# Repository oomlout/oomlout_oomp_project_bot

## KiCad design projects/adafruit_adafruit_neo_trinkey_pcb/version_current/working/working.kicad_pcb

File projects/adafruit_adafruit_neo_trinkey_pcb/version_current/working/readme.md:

# OOMP Project  
## Adafruit-Neo-Trinkey-PCB  by adafruit  
  
oomp key: oomp_projects_flat_adafruit_adafruit_neo_trinkey_pcb  
(snippet of original readme)  
  
-- Adafruit Neo Trinkey PCB  
  
<a href="http://www.adafruit.com/products/4870"><br/>  
Click here to purchase one from the Adafruit shop</a>  
  
PCB files for the Adafruit Neo Trinkey.   
  
Format is EagleCAD schematic and board layout  
* https://www.adafruit.com/product/4870  
  
--- Description  
  
It's half USB Key, half Adafruit Trinket...it's Neo Trinkey, the circuit board with a Trinket M0 heart and  four RGB NeoPixels for customizable glow. We were inspired by some USB key flashlight boards that would turn any battery pack into an LED torch. So we thought, hey what if we made something like that but with fully programmable color NeoPixels? And this is what we came up with!  
  
The PCB is designed to slip into any USB A port on a computer or laptop. There's an ATSAMD21 microcontroller on board with just enough circuitry to keep it happy. One pin of the microcontroller connects to the four NeoPixel LEDs. Two other pins are used as capacitive touch inputs on the end - if you look carefully you can see the slotted end has left and right touch pads. A reset button lets you enter bootloader mode if necessary. That's it!  
  
The SAMD21 can run CircuitPython or Arduino very nicely - with existing NeoPixel and our FreeTouch libraries for the capacitive touch input. Over the USB connection you can have serial, MIDI or HID connectivity. The Neo Trinkey is perfect for simple projects that can use a few user inputs and colorful outputs. Maybe you'll set it  
  full source readme at [readme_src.md](readme_src.md)  
  
source repo at: [https://github.com/adafruit/Adafruit-Neo-Trinkey-PCB](https://github.com/adafruit/Adafruit-Neo-Trinkey-PCB)  
## Board  

## Schematic  

[schematic pdf](working_schematic.pdf)  
## Images

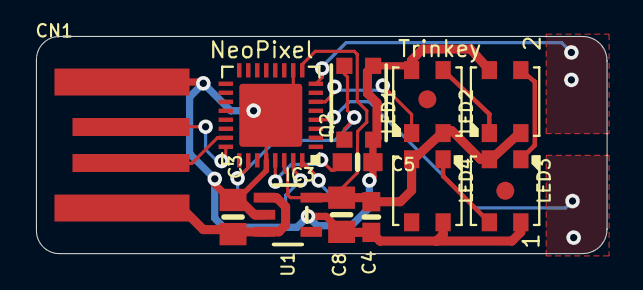
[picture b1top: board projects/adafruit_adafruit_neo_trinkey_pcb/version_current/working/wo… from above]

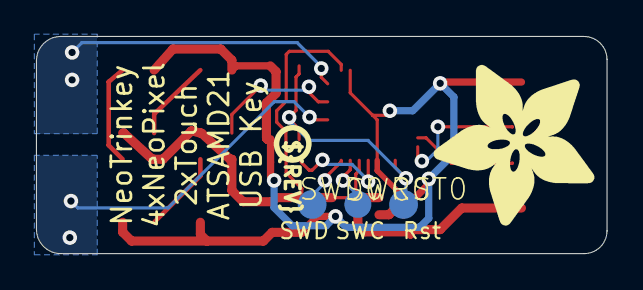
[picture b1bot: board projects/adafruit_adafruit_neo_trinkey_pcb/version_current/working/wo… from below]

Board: 2 copper layers, 31.7 x 12.1 mm, 19 parts (5 on the bottom side), 13 nets.

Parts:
C3, C8: 10uF; 0805-NO
C4, C5: 1uF; 0603-NO
CN1: USBA_PCB
FID1, FID2: FIDUCIAL_1MM
IC3: ATSAMD21E; QFN32_5MM
LED1, LED2, LED3, LED4: WS2812B3535; LED3535
Q2: reset; BTN_KMR2_4.6X2.8
RST0: TPTP16R; TP16R
SWC0: TPTP15R; TP15R
SWD0: TPTP16R; TP16R
U1: AP2112K-3.3; SOT23-5
U$8: PCBFEAT-REV-040
U$10: ADAFRUIT_9MM

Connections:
3.3V: C4.1, C8.1, IC3.9, IC3.30, LED1.2, LED2.2, LED3.2, LED4.2, U1.5
D+: CN1.USB_PLUS, IC3.24
D-: CN1.USB_NEG, IC3.23
GND: C3.2, C4.2, C5.2, C8.2, CN1.GND, IC3.10, IC3.28, IC3.33, LED1.4, LED2.4, LED3.4, LED4.4, Q2.B, Q2.B', U1.2
unnamed: LED1.3, LED2.1
unnamed: LED2.3, LED3.1
unnamed: LED3.3, LED4.1
NEOPIX: IC3.6, LED1.1
SWCLK: IC3.31, SWC0.TP
SWDIO: IC3.32, SWD0.TP
VBUS: C3.1, CN1.VCC, U1.1, U1.3
VDDCORE1: C5.1, IC3.29
~RESET: IC3.26, Q2.A, Q2.A', RST0.TP

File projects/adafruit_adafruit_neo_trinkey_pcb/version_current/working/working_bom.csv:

Row,Description,Part,References,Value,Footprint,Quantity Per PCB,Status,Datasheet
1,,CAP_CERAMIC0603_NO,C4 C5,1uF,0603-NO,2, ,
2,,CAP_CERAMIC0805-NOOUTLINE,C3 C8,10uF,0805-NO,2, ,
3,,USB_TYPEAPCB,CN1,USB_TYPEAPCB,USBA_PCB,1, ,
4,,ATSAMD21E,IC3,ATSAMD21E,QFN32_5MM,1, ,
5,,WS2812B3535,LED1 LED2 LED3 LED4,WS2812B3535,LED3535,4, ,
6,,SWITCH_TACT_SMT4.6X2.8,Q2,reset,BTN_KMR2_4.6X2.8,1, ,
7,,TPTP16R,RST0 SWD0,TPTP16R,TP16R,2, ,
8,,TPTP15R,SWC0,TPTP15R,TP15R,1, ,
9,,VREG_SOT23-5,U1,AP2112K-3.3,SOT23-5,1, ,





Project info:
Schematic:,working
Variant:,default
Revision:,
Date:,2023-08-03_17-21-22
KiCad Version:,7.0.6-7.0.6~ubuntu22.04.1
Statistics:
Component Groups:,9
Component Count:,15 (0 SMD/ 0 THT)
Fitted Components:,15 (0 SMD/ 0 THT)
Number of PCBs:,1
Total Components:,15

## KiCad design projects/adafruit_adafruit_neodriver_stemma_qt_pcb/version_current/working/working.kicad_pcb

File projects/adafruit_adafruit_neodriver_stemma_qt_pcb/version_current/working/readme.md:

# Adafruit-NeoDriver-STEMMA-QT-PCB by adafruit  
This is a harvested standardized copy of a project from github.  
The original project can be found at:  
https://github.com/adafruit/Adafruit-NeoDriver-STEMMA-QT-PCB  
Please consult that link for additional, details, files, and license information.  
Note: It was auto harvested and if the original repo had more than one board file or anything out of the ordinary the files here are likely not representative.

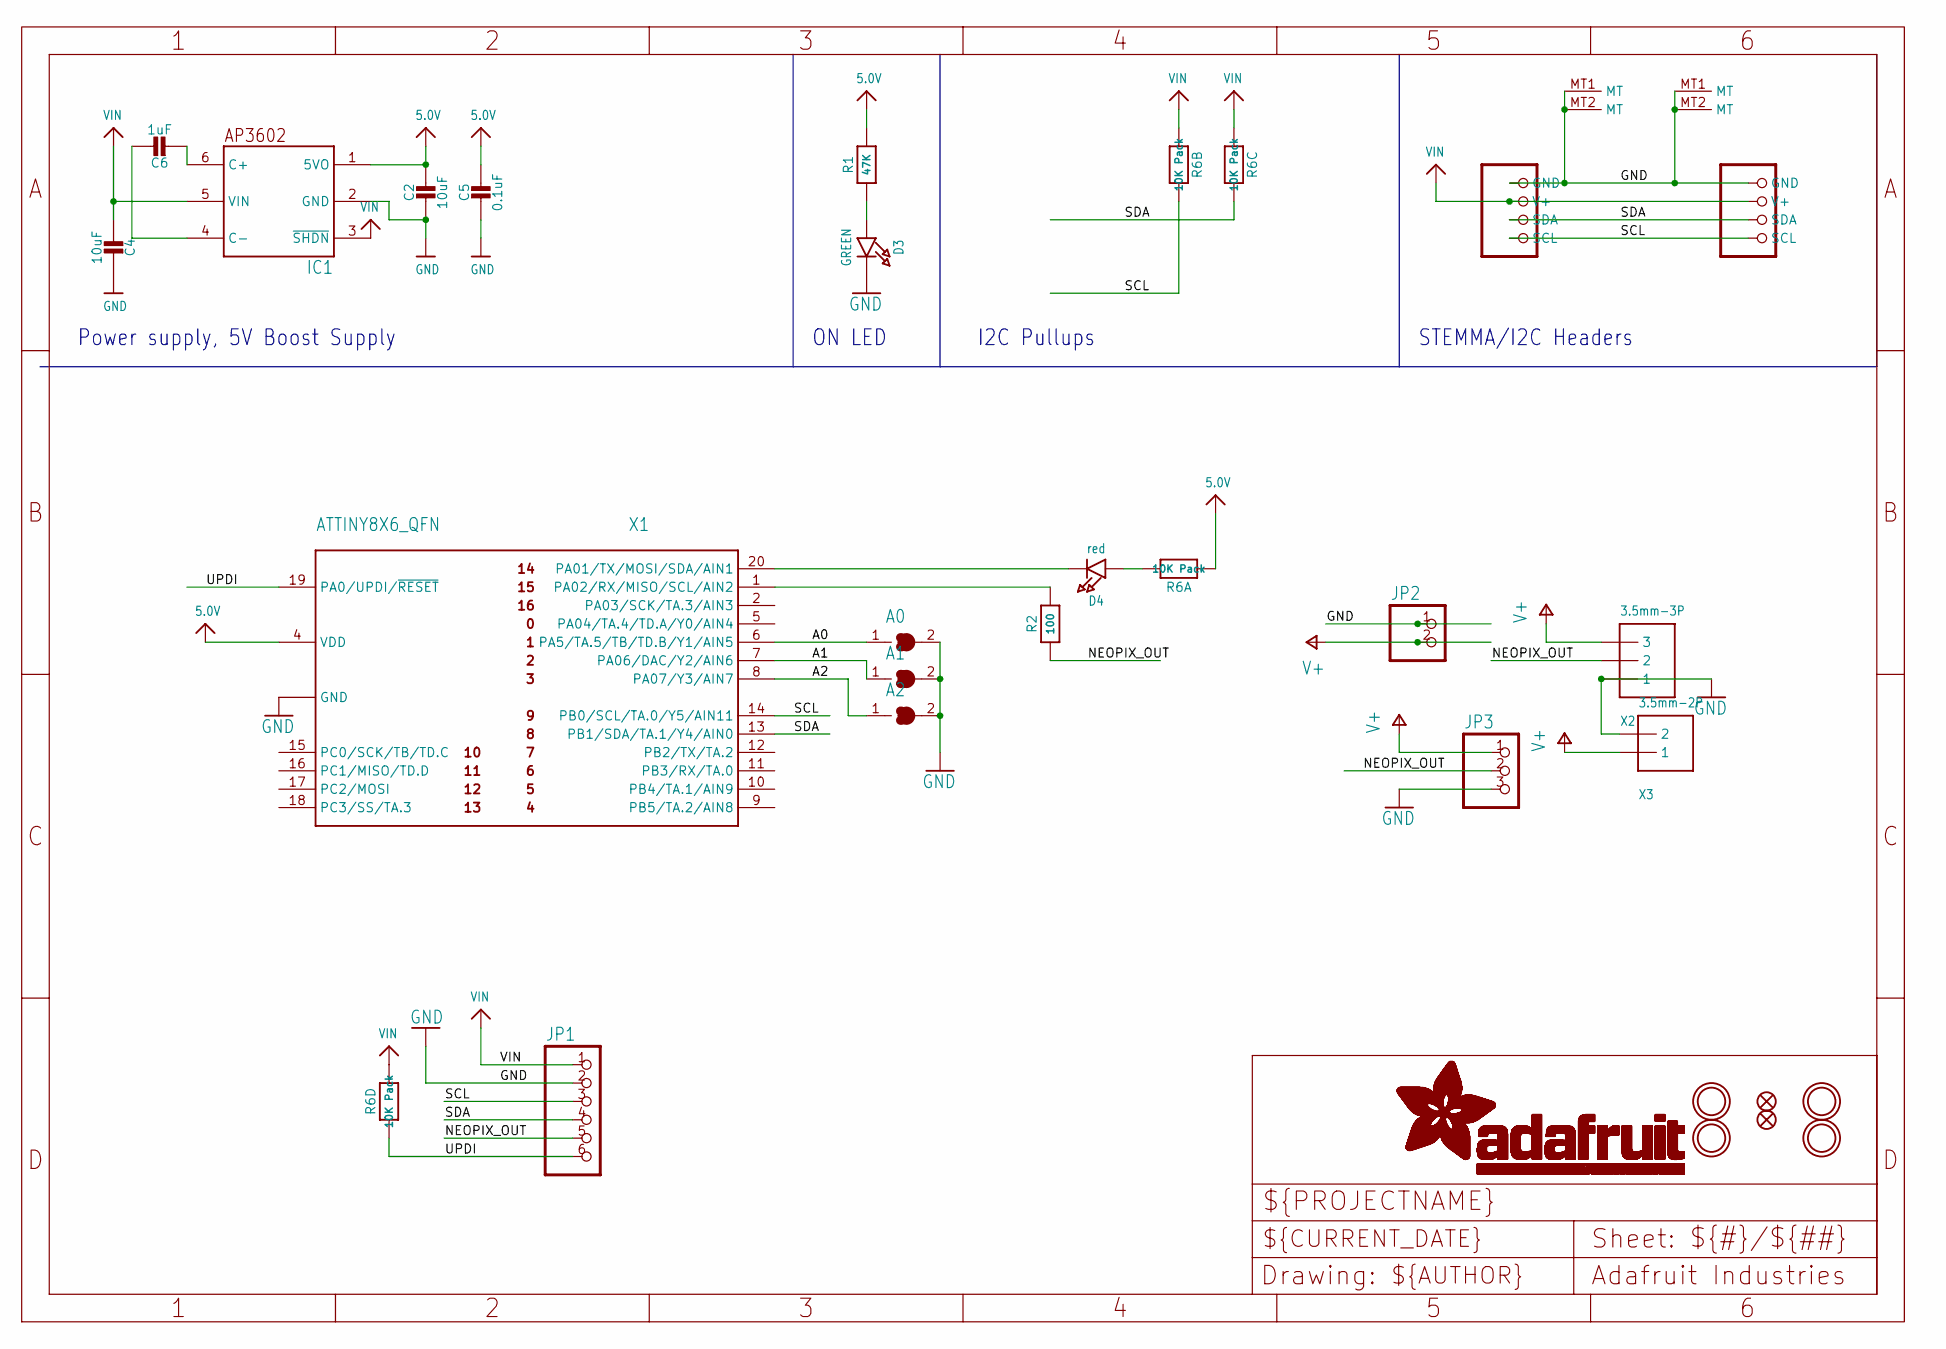
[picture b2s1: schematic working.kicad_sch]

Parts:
A0, A1, A2: SOLDERJUMPER_CLOSED; SOLDERJUMPER_CLOSEDWIRE
C2, C4: 10uF; 0805-NO
C5: 0.1uF; 0603-NO
C6: 1uF; 0603-NO
CONN3, CONN4: STEMMA_I2C_QT; JST_SH4
D3: GREEN; CHIPLED_0603_NOOUTLINE
D4: red; CHIPLED_0603_NOOUTLINE
FID1, FID2: FIDUCIAL_1MM
IC1: AP3602; SOT23-6
JP1: HEADER-1X670MIL; 1X06_ROUND_70
JP2: HEADER-1X2ROUND; 1X02_ROUND
JP3: HEADER-1X3ROUND; 1X03_ROUND
R1: 47K; 0603-NO
R2: 100; 0603-NO
R6: 10K Pack; RESPACK_4X0603
U$1, U$6, U$9, U$18: MOUNTINGHOLE2.5; MOUNTINGHOLE_2.5_PLATED
X1: ATTINY8X6_QFN; QFN20_3MM
X2: 3.5mm-3P; TERMBLOCK_1X3-3.5MM
X3: 3.5mm-2P; TERMBLOCK_1X2-3.5MM

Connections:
5.0V: C2.1, C5.1, IC1.1 (5VO), R1.2, R6.1, X1.4 (VDD)
A0: A0.1, X1.6 (PA5/TA.5/TB/TD.B/Y1/AIN5)
A1: A1.1, X1.7 (PA06/DAC/Y2/AIN6)
A2: A2.1, X1.8 (PA07/Y3/AIN7)
ACT: D4.C, X1.20 (PA01/TX/MOSI/SDA/AIN1)
GND: A0.2, A1.2, A2.2, C2.2, C4.2, C5.2, CONN3.1 (GND), CONN3.MT1 (MT), CONN3.MT2 (MT), CONN4.1 (GND), CONN4.MT1 (MT), CONN4.MT2 (MT), D3.C, IC1.2 (GND), JP1.2, JP2.1, JP3.3, X1.3 (GND), X1.PAD (GND), X2.1, X3.2
unnamed: D3.A, R1.1
unnamed: C6.2, IC1.6 (C+)
unnamed: C6.1, IC1.4 (C-)
unnamed: D4.A, R6.8 (2)
unnamed: R2.2, X1.1 (PA02/RX/MISO/SCL/AIN2)
NEOPIX_OUT: JP1.5, JP3.2, R2.1, X2.2
SCL: CONN3.4 (SCL), CONN4.4 (SCL), JP1.3, R6.7 (2), X1.14 (PB0/SCL/TA.0/Y5/AIN11)
SDA: CONN3.3 (SDA), CONN4.3 (SDA), JP1.4, R6.6 (2), X1.13 (PB1/SDA/TA.1/Y4/AIN0)
UPDI: JP1.6, R6.4 (1), X1.19 (PA0/UPDI/~RESET)
V+: JP2.2, JP3.1, X2.3, X3.1
VIN: C4.1, CONN3.2 (V+), CONN4.2 (V+), IC1.3 (~SHDN), IC1.5 (VIN), JP1.1, R6.2 (1), R6.3 (1), R6.5 (2)

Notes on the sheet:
ON LED
Power supply, 5V Boost Supply
I2C Pullups
STEMMA/I2C Headers

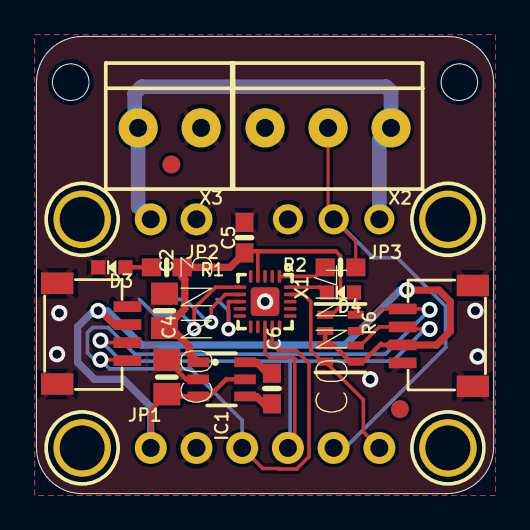
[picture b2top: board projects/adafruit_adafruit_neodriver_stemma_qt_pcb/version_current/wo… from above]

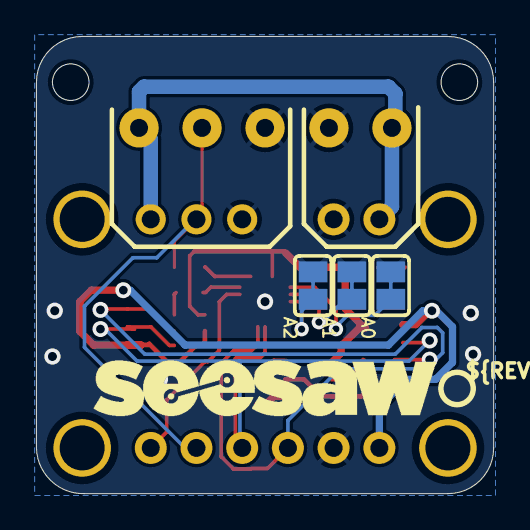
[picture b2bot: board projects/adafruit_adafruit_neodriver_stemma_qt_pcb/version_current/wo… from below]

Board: 2 copper layers, 25.4 x 25.4 mm, 61 parts (17 on the bottom side), 17 nets.

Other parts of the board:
@HOLE0, @HOLE1: (no value)
PLABEL0: PLABEL0
PLABEL1: PLABEL1
PLABEL2: PLABEL2
PLABEL3: PLABEL3
PLABEL4: PLABEL4
PLABEL5: PLABEL5
PLABEL6: PLABEL6
PLABEL7: PLABEL7
PLABEL8: PLABEL8
PLABEL9: PLABEL9
PLABEL10: PLABEL10
PLABEL11: PLABEL11
PLABEL12: PLABEL12
PLABEL13: PLABEL13
PLABEL14: PLABEL14
PLABEL15: PLABEL15
PLABEL16: PLABEL16
PLABEL17: PLABEL17
PLABEL18: PLABEL18
PLABEL19: PLABEL19
PLABEL20: PLABEL20
PLABEL21: PLABEL21
PLABEL22: PLABEL22
PLABEL23: PLABEL23
PLABEL24: PLABEL24
PLABEL25: PLABEL25
PLABEL26: PLABEL26
PLABEL27: PLABEL27
PLABEL28: PLABEL28
PLABEL29: PLABEL29
U$7: SEESAW_LOGO
U$12: PCBFEAT-REV-040

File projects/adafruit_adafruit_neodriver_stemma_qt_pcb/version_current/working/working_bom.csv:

Row,Description,Part,References,Value,Footprint,Quantity Per PCB,Status,Datasheet
1,,CAP_CERAMIC0603_NO,C5,0.1uF,0603-NO,1, ,
2,,CAP_CERAMIC0603_NO,C6,1uF,0603-NO,1, ,
3,,CAP_CERAMIC0805-NOOUTLINE,C2 C4,10uF,0805-NO,2, ,
4,,STEMMA_I2C_QT,CONN3 CONN4,STEMMA_I2C_QT,JST_SH4,2, ,
5,,LED0603_NOOUTLINE,D3,GREEN,CHIPLED_0603_NOOUTLINE,1, ,
6,,LED0603_NOOUTLINE,D4,red,CHIPLED_0603_NOOUTLINE,1, ,
7,,AP3602,IC1,AP3602,SOT23-6,1, ,
8,,HEADER-1X2ROUND,JP2,HEADER-1X2ROUND,1X02_ROUND,1, ,
9,,HEADER-1X3ROUND,JP3,HEADER-1X3ROUND,1X03_ROUND,1, ,
10,,HEADER-1X670MIL,JP1,HEADER-1X670MIL,1X06_ROUND_70,1, ,
11,,RESISTOR_0603_NOOUT,R2,100,0603-NO,1, ,
12,,RESISTOR_4PACK,R6,10K Pack,RESPACK_4X0603,1, ,
13,,RESISTOR_0603_NOOUT,R1,47K,0603-NO,1, ,
14,,TERMBLOCK_1X2_3.5MM,X3,3.5mm-2P,TERMBLOCK_1X2-3.5MM,1, ,
15,,TERMBLOCK_1X3,X2,3.5mm-3P,TERMBLOCK_1X3-3.5MM,1, ,
16,,ATTINY8X6_QFN,X1,ATTINY8X6_QFN,QFN20_3MM,1, ,





Project info:
Schematic:,working
Variant:,default
Revision:,
Date:,2023-08-03_17-21-22
KiCad Version:,7.0.6-7.0.6~ubuntu22.04.1
Statistics:
Component Groups:,16
Component Count:,18 (0 SMD/ 0 THT)
Fitted Components:,18 (0 SMD/ 0 THT)
Number of PCBs:,1
Total Components:,18

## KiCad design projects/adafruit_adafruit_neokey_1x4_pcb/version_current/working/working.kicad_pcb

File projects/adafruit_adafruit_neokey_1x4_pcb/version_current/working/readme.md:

# Adafruit-NeoKey-1x4-PCB by adafruit  
This is a harvested standardized copy of a project from github.  
The original project can be found at:  
https://github.com/adafruit/Adafruit-NeoKey-1x4-PCB  
Please consult that link for additional, details, files, and license information.  
Note: It was auto harvested and if the original repo had more than one board file or anything out of the ordinary the files here are likely not representative.

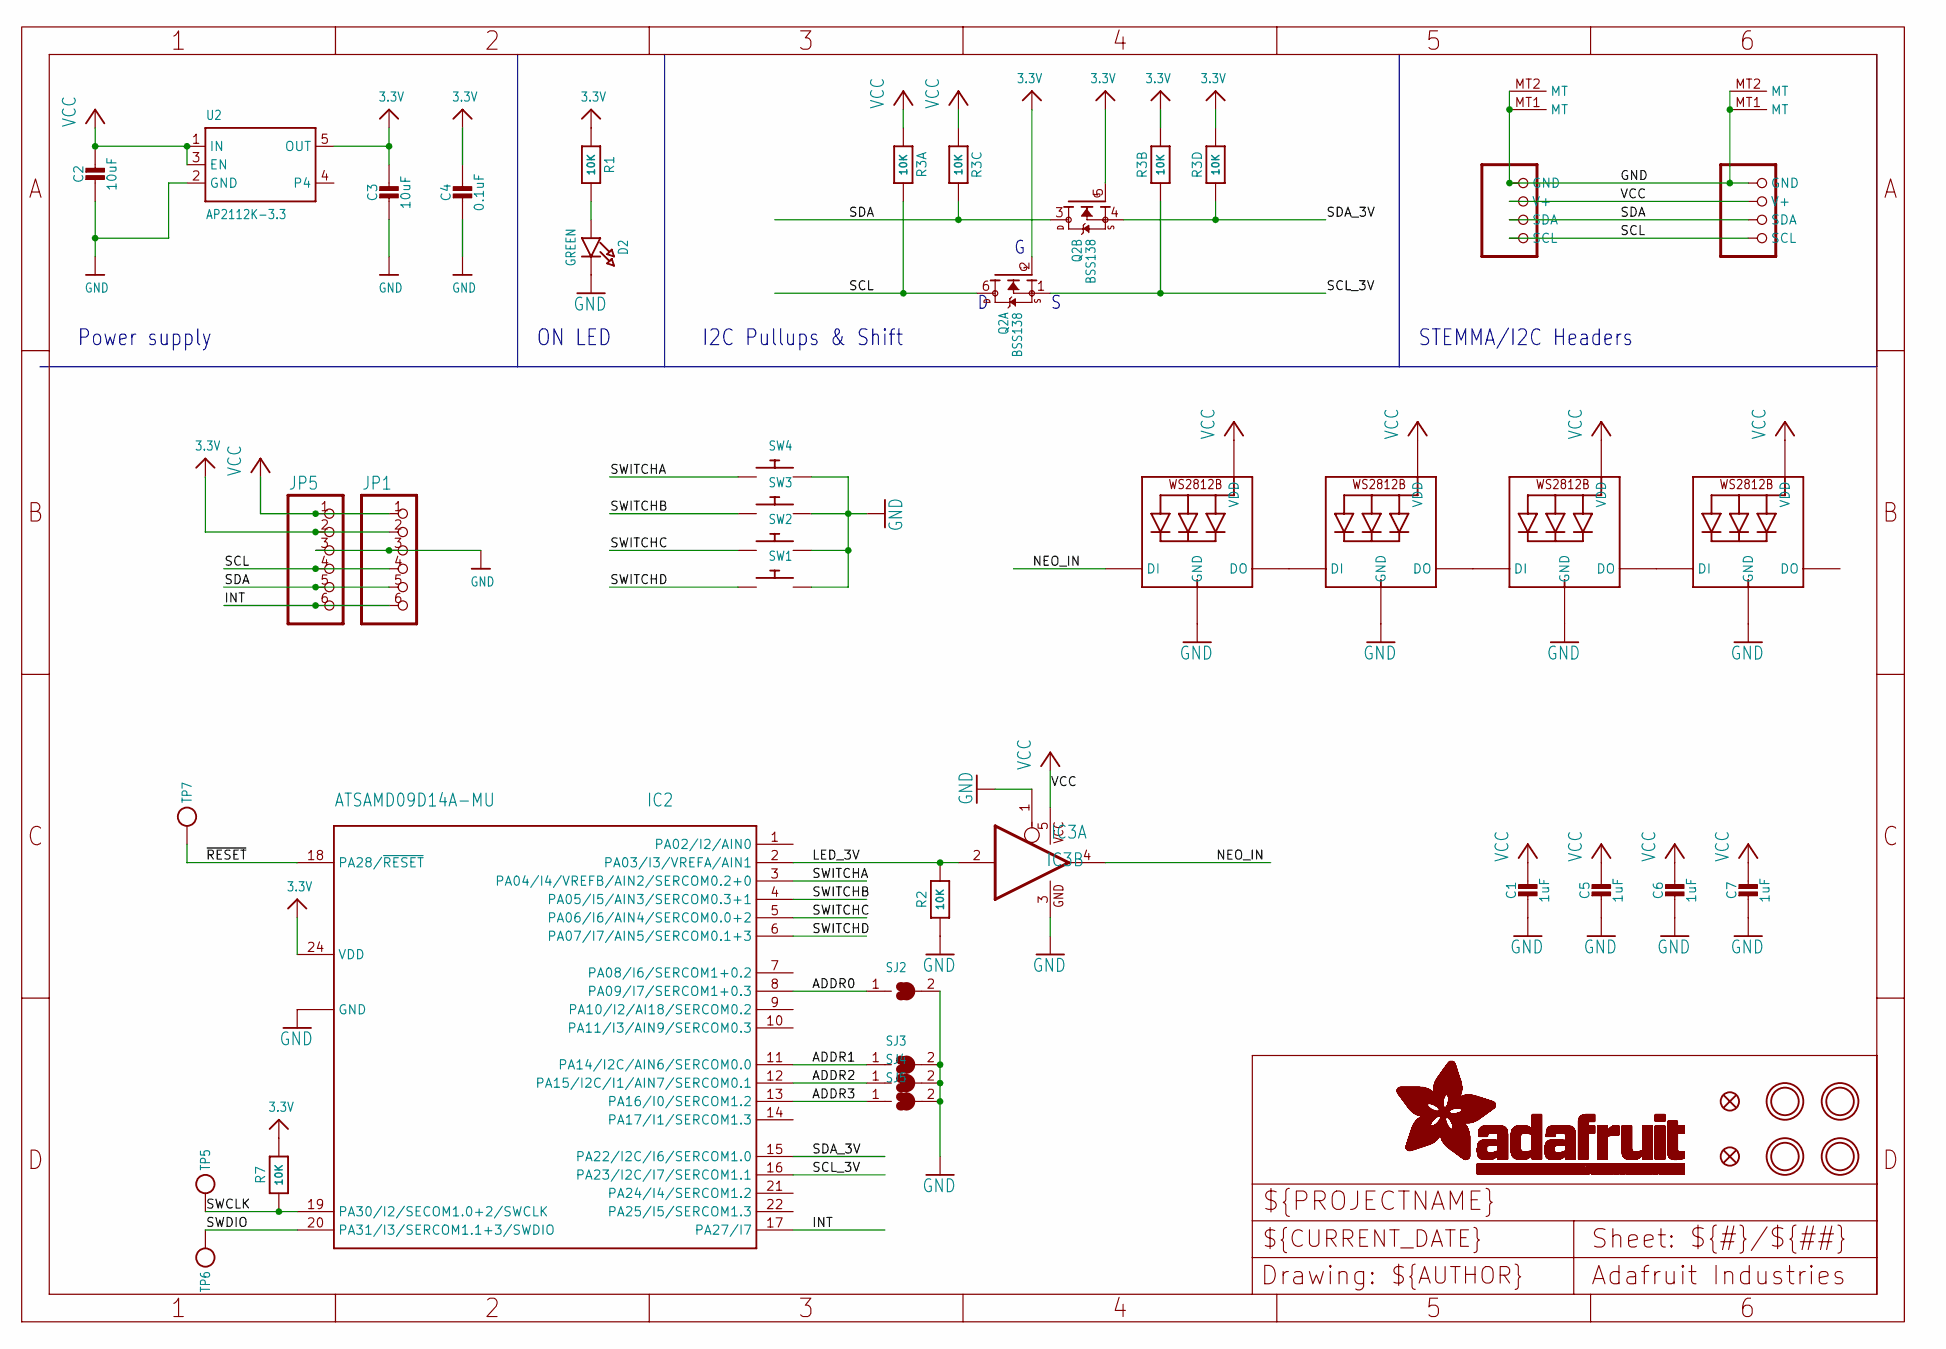
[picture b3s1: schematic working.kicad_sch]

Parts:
C1, C5, C6, C7: 1uF; 0603-NO
C2, C3: 10uF; 0805-NO
C4: 0.1uF; 0603-NO
CONN3, CONN4: STEMMA_I2C_QT; JST_SH4
D2: GREEN; CHIPLED_0603_NOOUTLINE
FID1, FID2: FIDUCIAL_1MM
IC2: ATSAMD09D14A-MU; QFN24_4MM
IC3: 741G125DBV; SOT23-5
JP1, JP5: HEADER-1X670MIL; 1X06_ROUND_70
LED1, LED2, LED3, LED4: WS2812B_SK6812E; NEO3535_REVERSE
Q2: BSS138; SOT363
R1, R2, R7: 10K; 0603-NO
R3: 10K; RESPACK_4X0603
SJ2, SJ3, SJ4, SJ5: SOLDERJUMPER; SOLDERJUMPER_ARROW_NOPASTE
SW1, SW2, SW3, SW4: SWITCH_PUSHBUTTON_KAILH_SOCKET; KAILH_SOCKET
TP5, TP6, TP7: TESTPOINTROUND1.5MM; TESTPOINT_ROUND_1.5MM
U2: AP2112K-3.3; SOT23-5
U$3, U$17, U$19, U$21: MOUNTINGHOLE2.5; MOUNTINGHOLE_2.5_PLATED

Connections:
3.3V: C3.1, C4.1, IC2.24 (VDD), JP1.2, JP5.2, Q2.2 (G), Q2.5 (G), R1.1, R3.2 (1), R3.4 (1), R7.2, U2.5 (OUT)
ADDR0: IC2.8 (PA09/I7/SERCOM1+0.3), SJ2.1
ADDR1: IC2.11 (PA14/I2C/AIN6/SERCOM0.0), SJ3.1
ADDR2: IC2.12 (PA15/I2C/I1/AIN7/SERCOM0.1), SJ4.1
ADDR3: IC2.13 (PA16/I0/SERCOM1.2), SJ5.1
GND: C1.2, C2.2, C3.2, C4.2, C5.2, C6.2, C7.2, CONN3.1 (GND), CONN3.MT1 (MT), CONN3.MT2 (MT), CONN4.1 (GND), CONN4.MT1 (MT), CONN4.MT2 (MT), D2.C, IC2.23 (GND), IC2.THERM (GND), IC3.1 (OE), IC3.3 (GND), JP1.3, JP5.3, LED1.3-GND (GND), LED2.3-GND (GND), LED3.3-GND (GND), LED4.3-GND (GND), R2.1, SJ2.2, SJ3.2, SJ4.2, SJ5.2, SW1.1, SW2.1, SW3.1, SW4.1, U2.2 (GND)
INT: IC2.17 (PA27/I7), JP1.6, JP5.6
LED_3V: IC2.2 (PA03/I3/VREFA/AIN1), IC3.2 (I), R2.2
unnamed: D2.A, R1.2
unnamed: LED1.2-DOUT (DO), LED2.4-DIN (DI)
unnamed: LED2.2-DOUT (DO), LED3.4-DIN (DI)
unnamed: LED3.2-DOUT (DO), LED4.4-DIN (DI)
NEO_IN: IC3.4 (O), LED1.4-DIN (DI)
SCL: CONN3.4 (SCL), CONN4.4 (SCL), JP1.4, JP5.4, Q2.6 (D), R3.8 (2)
SCL_3V: IC2.16 (PA23/I2C/I7/SERCOM1.1), Q2.1 (S), R3.7 (2)
SDA: CONN3.3 (SDA), CONN4.3 (SDA), JP1.5, JP5.5, Q2.3 (D), R3.6 (2)
SDA_3V: IC2.15 (PA22/I2C/I6/SERCOM1.0), Q2.4 (S), R3.5 (2)
SWCLK: IC2.19 (PA30/I2/SECOM1.0+2/SWCLK), R7.1, TP5.P$1
SWDIO: IC2.20 (PA31/I3/SERCOM1.1+3/SWDIO), TP6.P$1
SWITCHA: IC2.3 (PA04/I4/VREFB/AIN2/SERCOM0.2+0), SW4.2
SWITCHB: IC2.4 (PA05/I5/AIN3/SERCOM0.3+1), SW3.2
SWITCHC: IC2.5 (PA06/I6/AIN4/SERCOM0.0+2), SW2.2
SWITCHD: IC2.6 (PA07/I7/AIN5/SERCOM0.1+3), SW1.2
VCC: C1.1, C2.1, C5.1, C6.1, C7.1, CONN3.2 (V+), CONN4.2 (V+), IC3.5 (VCC), JP1.1, JP5.1, LED1.1-VDD (VDD), LED2.1-VDD (VDD), LED3.1-VDD (VDD), LED4.1-VDD (VDD), R3.1, R3.3 (1), U2.1 (IN), U2.3 (EN)
~RESET: IC2.18 (PA28/~RESET), TP7.P$1

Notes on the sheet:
ON LED
I2C Pullups & Shift
Power supply
STEMMA/I2C Headers

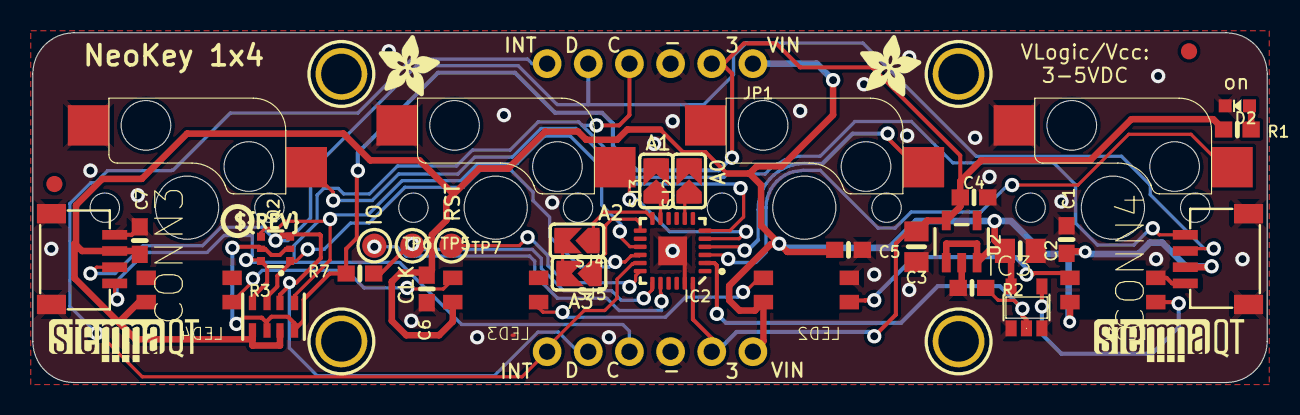
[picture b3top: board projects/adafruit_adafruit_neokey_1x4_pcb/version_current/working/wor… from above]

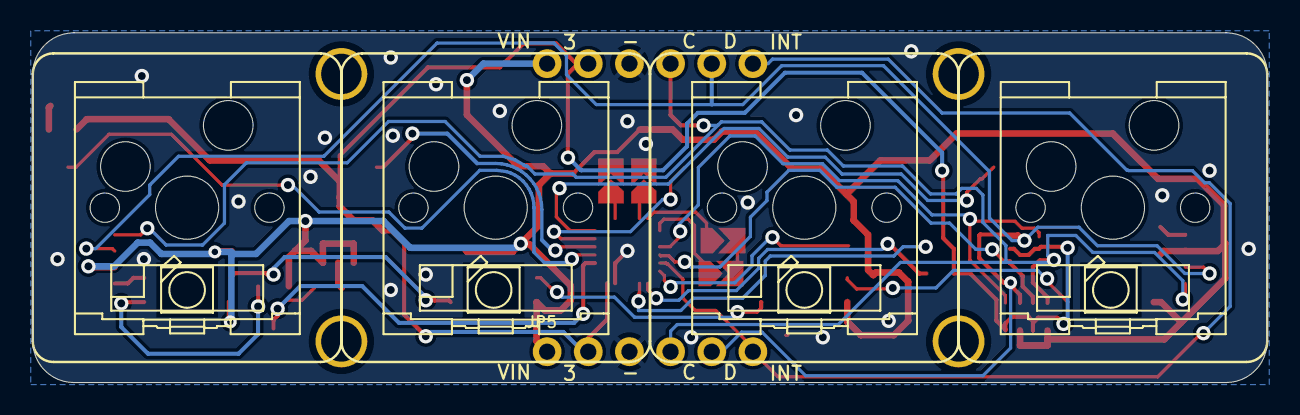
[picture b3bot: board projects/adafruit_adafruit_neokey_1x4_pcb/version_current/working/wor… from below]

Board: 2 copper layers, 76.2 x 21.6 mm, 46 parts (9 on the bottom side), 25 nets.

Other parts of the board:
U$2, U$9: ADAFRUIT_3.5MM
U$25: PCBFEAT-REV-040
U$30, U$31: STEMMAQT

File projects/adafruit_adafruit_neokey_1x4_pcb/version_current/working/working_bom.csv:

Row,Description,Part,References,Value,Footprint,Quantity Per PCB,Status,Datasheet
1,,CAP_CERAMIC0603_NO,C4,0.1uF,0603-NO,1, ,
2,,CAP_CERAMIC0603_NO,C1 C5 C6 C7,1uF,0603-NO,4, ,
3,,CAP_CERAMIC0805-NOOUTLINE,C2 C3,10uF,0805-NO,2, ,
4,,STEMMA_I2C_QT,CONN3 CONN4,STEMMA_I2C_QT,JST_SH4,2, ,
5,,LED0603_NOOUTLINE,D2,GREEN,CHIPLED_0603_NOOUTLINE,1, ,
6,,741G125DBV,IC3,741G125DBV,SOT23-5,1, ,
7,,ATSAMD09D14A-MU,IC2,ATSAMD09D14A-MU,QFN24_4MM,1, ,
8,,HEADER-1X670MIL,JP1 JP5,HEADER-1X670MIL,1X06_ROUND_70,2, ,
9,,WS2812B_SK6812E,LED1 LED2 LED3 LED4,WS2812B_SK6812E,NEO3535_REVERSE,4, ,
10,,MOSFET-N_DUAL,Q2,BSS138,SOT363,1, ,
11,,RESISTOR_0603_NOOUT,R1 R2 R7,10K,0603-NO,3, ,
12,,RESISTOR_4PACK,R3,10K,RESPACK_4X0603,1, ,
13,,SWITCH_PUSHBUTTON_KAILH_SOCKET,SW1 SW2 SW3 SW4,SWITCH_PUSHBUTTON_KAILH_SOCKET,KAILH_SOCKET,4, ,
14,,VREG_SOT23-5,U2,AP2112K-3.3,SOT23-5,1, ,





Project info:
Schematic:,working
Variant:,default
Revision:,
Date:,2023-08-03_17-21-22
KiCad Version:,7.0.6-7.0.6~ubuntu22.04.1
Statistics:
Component Groups:,14
Component Count:,28 (0 SMD/ 0 THT)
Fitted Components:,28 (0 SMD/ 0 THT)
Number of PCBs:,1
Total Components:,28

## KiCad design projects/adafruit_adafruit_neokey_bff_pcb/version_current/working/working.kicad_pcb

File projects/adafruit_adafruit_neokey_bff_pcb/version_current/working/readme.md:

# OOMP Project  
## Adafruit-NeoKey-BFF-PCB  by adafruit  
  
oomp key: oomp_projects_flat_adafruit_adafruit_neokey_bff_pcb  
(snippet of original readme)  
  
-- Adafruit NeoKey BFF for Mechanical Key Add-On for QT Py and Xiao - For MX Compatible Switches PCB  
  
<a href="http://www.adafruit.com/products/5695"><br/>  
Click here to purchase one from the Adafruit shop</a>  
  
PCB files for the Adafruit NeoKey BFF for Mechanical Key Add-On for QT Py and Xiao - For MX Compatible Switches.   
  
Format is EagleCAD schematic and board layout  
* https://www.adafruit.com/product/5695  
  
--- Description  
  
Our QT Py boards are a great way to make very small microcontroller projects that pack a ton of power - and now we have a way for you to quickly add a nice mechanical key that also can glow any color of the rainbow.   
  
We call this the Adafruit NeoKey BFF - a "Best Friend Forever". When you were a kid you may have learned about the "buddy" system, well this product is kinda like that! A board that will watch your QT Py's back and give it more capabilities.  
  
This PCB is designed to fit onto the back of any QT Py or Xiao board; it can be soldered into place or use pin and socket headers to make it removable. Onboard is a Kailh socket, which means you can plug in any MX-compatible switch instead of soldering it in. You may need a little glue to keep the switch in place: hot glue or a dot of epoxy worked fine for us. Also comes with a single reverse-mount NeoPixel pointing up through the spot where many switches would have an LED to shine through.  
  
We include some header that you can solder to your QT Py. Y  
  full source readme at [readme_src.md](readme_src.md)  
  
source repo at: [https://github.com/adafruit/Adafruit-NeoKey-BFF-PCB](https://github.com/adafruit/Adafruit-NeoKey-BFF-PCB)  
## Board  

## Schematic  

[schematic pdf](working_schematic.pdf)  
## Images

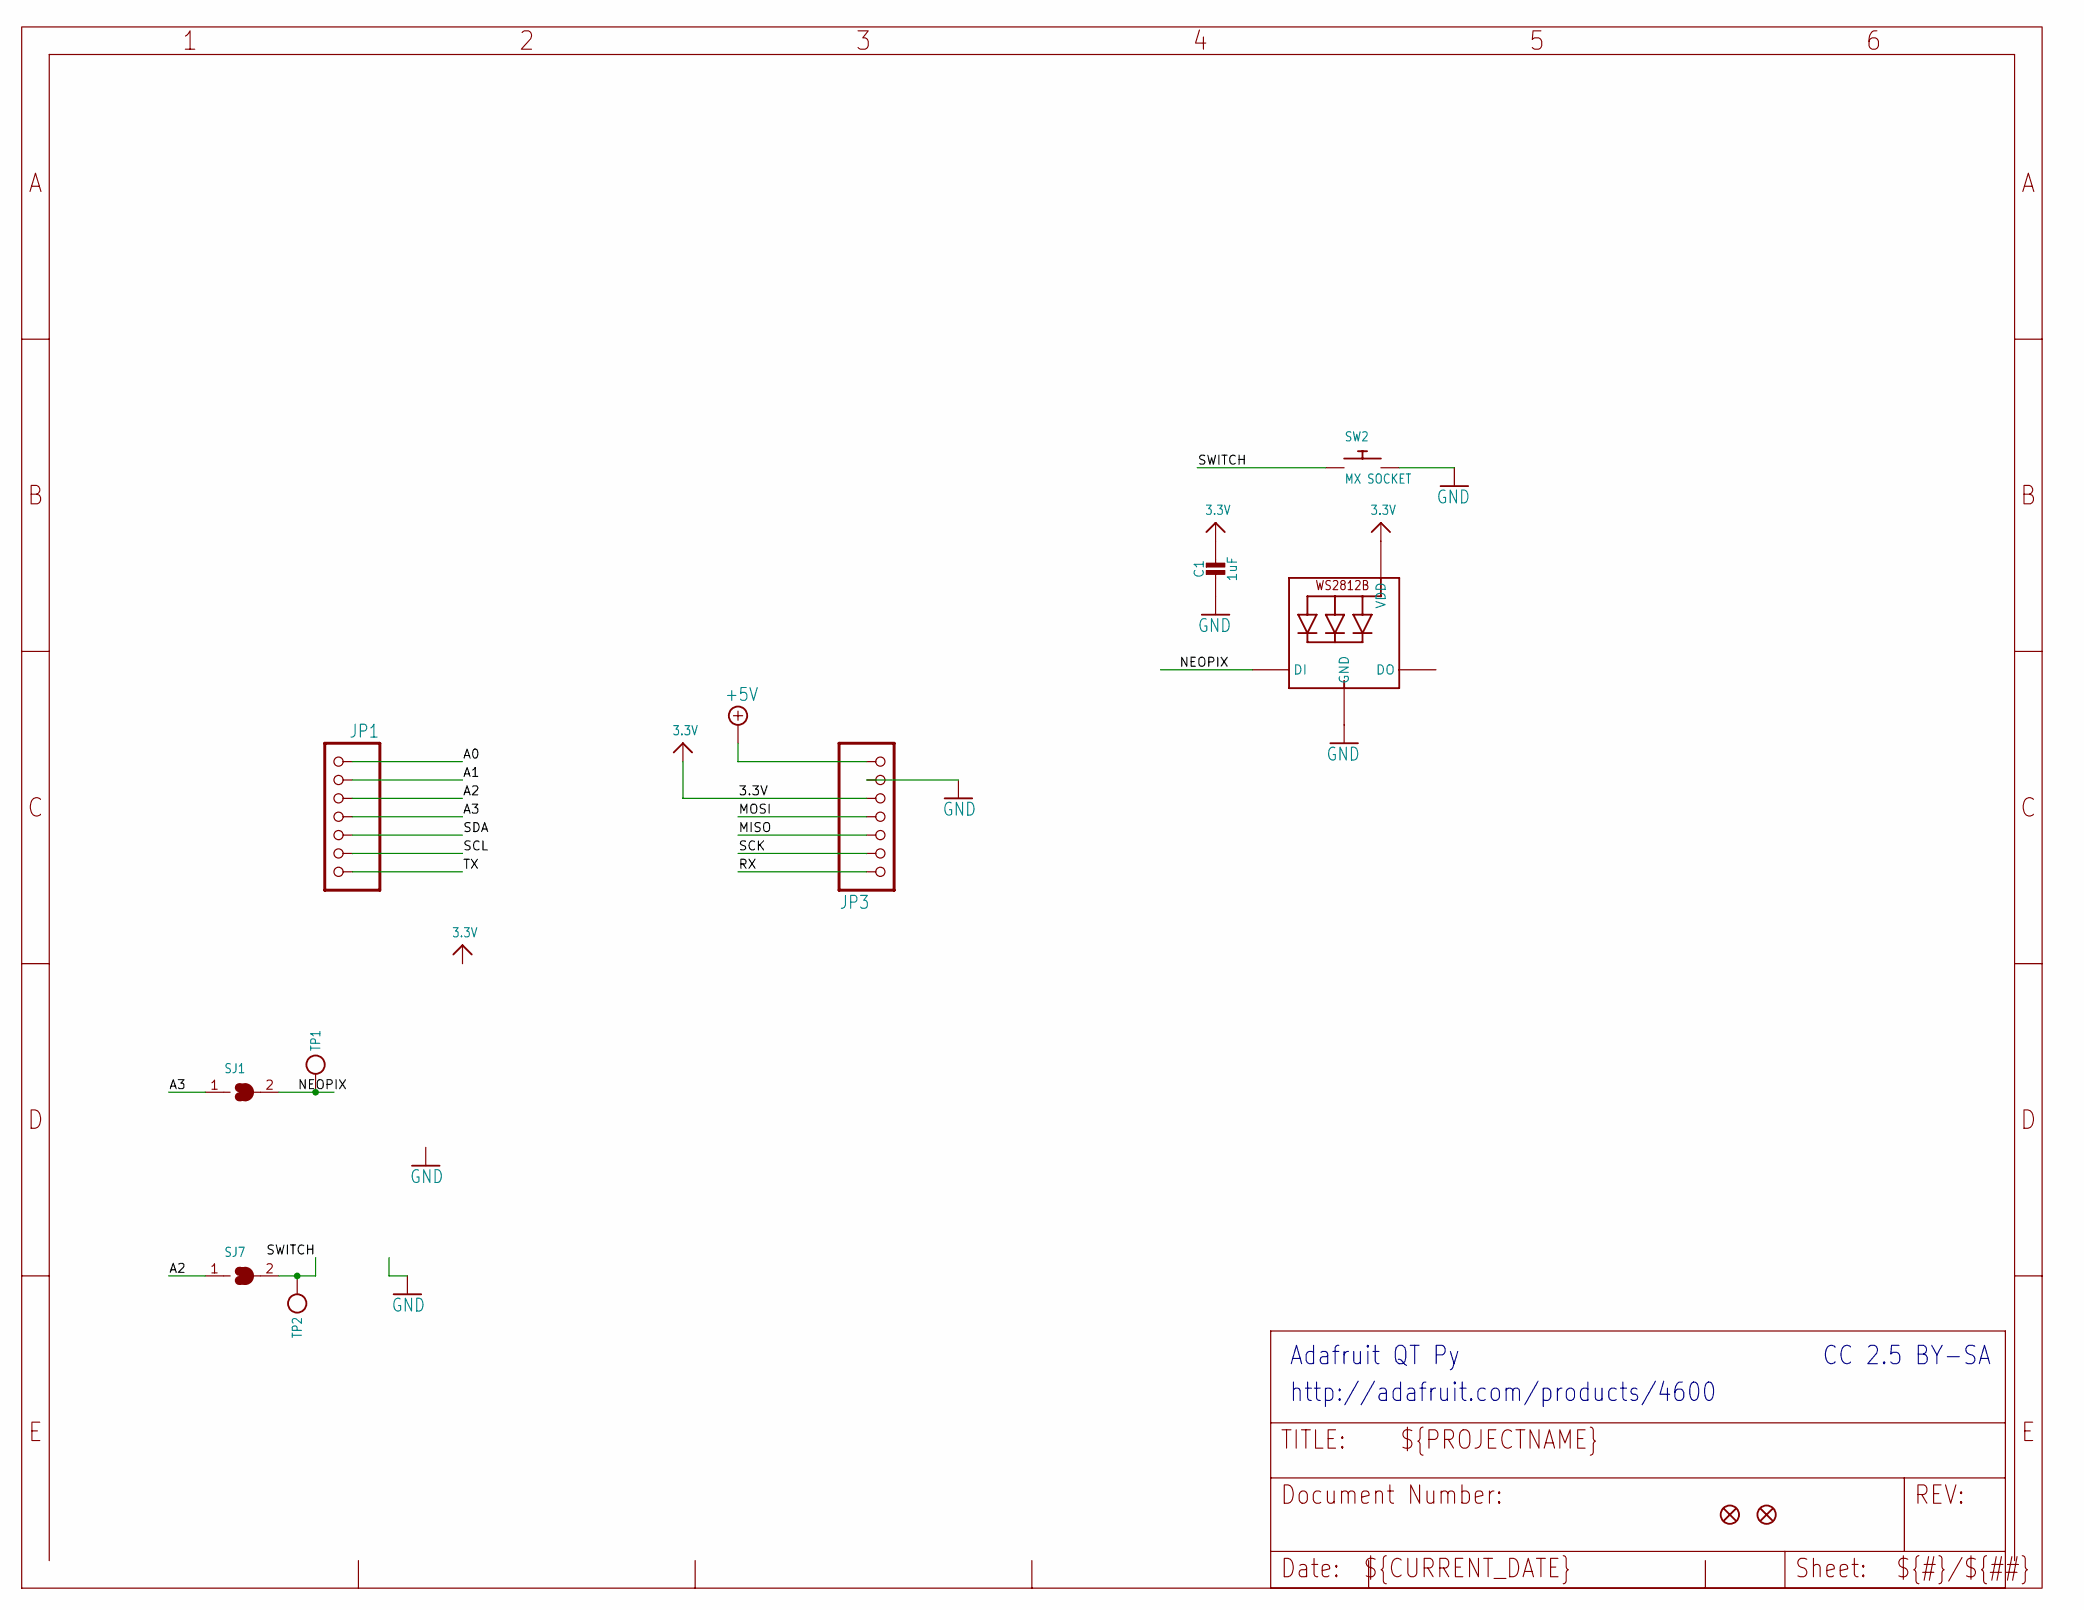
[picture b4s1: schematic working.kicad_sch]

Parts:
C1: 1uF; 0603-NO
JP1, JP3: HEADER-1X7_CASTEL; 1X07_CASTEL
LED2: WS2812B_SK6812E; NEO3535_REVERSE
SJ1, SJ7: SOLDERJUMPERCLOSED; SOLDERJUMPER_CLOSEDWIRE
SW2: MX SOCKET; KAILH_SOCKET
TP1, TP2: TESTPOINT1.5X2.0MM_NOCREAM; PAD-1.5X2.0
U$6, U$8: FIDUCIAL_1MM

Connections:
3.3V: C1.1, JP3.5, JP3.5C (5), LED2.1-VDD (VDD)
+5V: JP3.7, JP3.7C (7)
A0: JP1.1, JP1.1C (1)
A1: JP1.2, JP1.2C (2)
A2: JP1.3, JP1.3C (3), SJ7.1
A3: JP1.4, JP1.4C (4), SJ1.1
GND: C1.2, JP3.6, JP3.6C (6), LED2.3-GND (GND), SW2.2
MISO: JP3.3, JP3.3C (3)
MOSI: JP3.4, JP3.4C (4)
NEOPIX: LED2.4-DIN (DI), SJ1.2, TP1.P$1
RX: JP3.1, JP3.1C (1)
SCK: JP3.2, JP3.2C (2)
SCL: JP1.6, JP1.6C (6)
SDA: JP1.5, JP1.5C (5)
SWITCH: SJ7.2, SW2.1, TP2.P$1
TX: JP1.7, JP1.7C (7)

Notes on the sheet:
Adafruit QT Py
http://adafruit.com/products/4600
CC 2.5 BY-SA

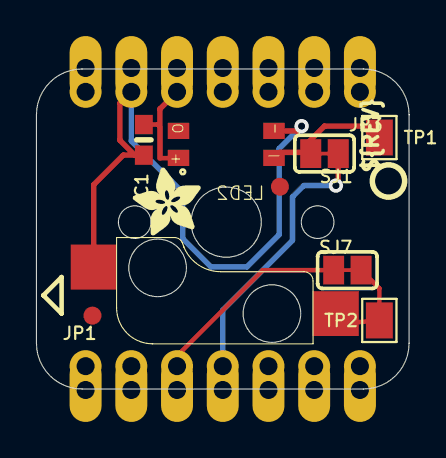
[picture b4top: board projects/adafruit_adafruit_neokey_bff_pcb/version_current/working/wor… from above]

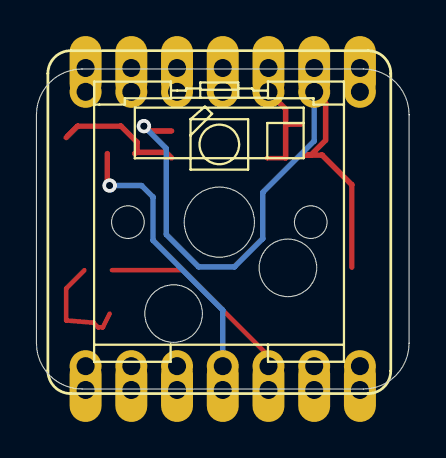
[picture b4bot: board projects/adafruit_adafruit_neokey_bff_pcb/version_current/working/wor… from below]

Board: 16 copper layers, 20.7 x 17.8 mm, 23 parts (2 on the bottom side), 16 nets.

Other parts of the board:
PLABEL0: PLABEL0
PLABEL1: PLABEL1
PLABEL2: PLABEL2
PLABEL3: PLABEL3
PLABEL4: PLABEL4
PLABEL5: PLABEL5
PLABEL6: PLABEL6
PLABEL7: PLABEL7
PLABEL8: PLABEL8
PLABEL9: PLABEL9
U$2: ADAFRUIT_3.5MM
U$3: PCBFEAT-REV-040

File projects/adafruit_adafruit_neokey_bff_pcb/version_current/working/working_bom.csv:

Row,Description,Part,References,Value,Footprint,Quantity Per PCB,Status,Datasheet,XOFFSET
1,,CAP_CERAMIC0603_NO,C1,1uF,0603-NO,1, ,,
2,,HEADER-1X7_CASTEL,JP1 JP3,HEADER-1X7_CASTEL,1X07_CASTEL,2, ,,
3,,WS2812B_SK6812E,LED2,WS2812B_SK6812E,NEO3535_REVERSE,1, ,,
4,,SWITCH_PUSHBUTTON_KAILH_SOCKET,SW2,MX SOCKET,KAILH_SOCKET,1, ,,-.75





Project info:
Schematic:,working
Variant:,default
Revision:,
Date:,2023-08-03_17-21-22
KiCad Version:,7.0.6-7.0.6~ubuntu22.04.1
Statistics:
Component Groups:,4
Component Count:,5 (0 SMD/ 0 THT)
Fitted Components:,5 (0 SMD/ 0 THT)
Number of PCBs:,1
Total Components:,5

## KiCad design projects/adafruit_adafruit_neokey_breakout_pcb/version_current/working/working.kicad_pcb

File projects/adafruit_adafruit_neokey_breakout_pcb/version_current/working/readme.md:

# Adafruit-NeoKey-Breakout-PCB by adafruit  
This is a harvested standardized copy of a project from github.  
The original project can be found at:  
https://github.com/adafruit/Adafruit-NeoKey-Breakout-PCB  
Please consult that link for additional, details, files, and license information.  
Note: It was auto harvested and if the original repo had more than one board file or anything out of the ordinary the files here are likely not representative.

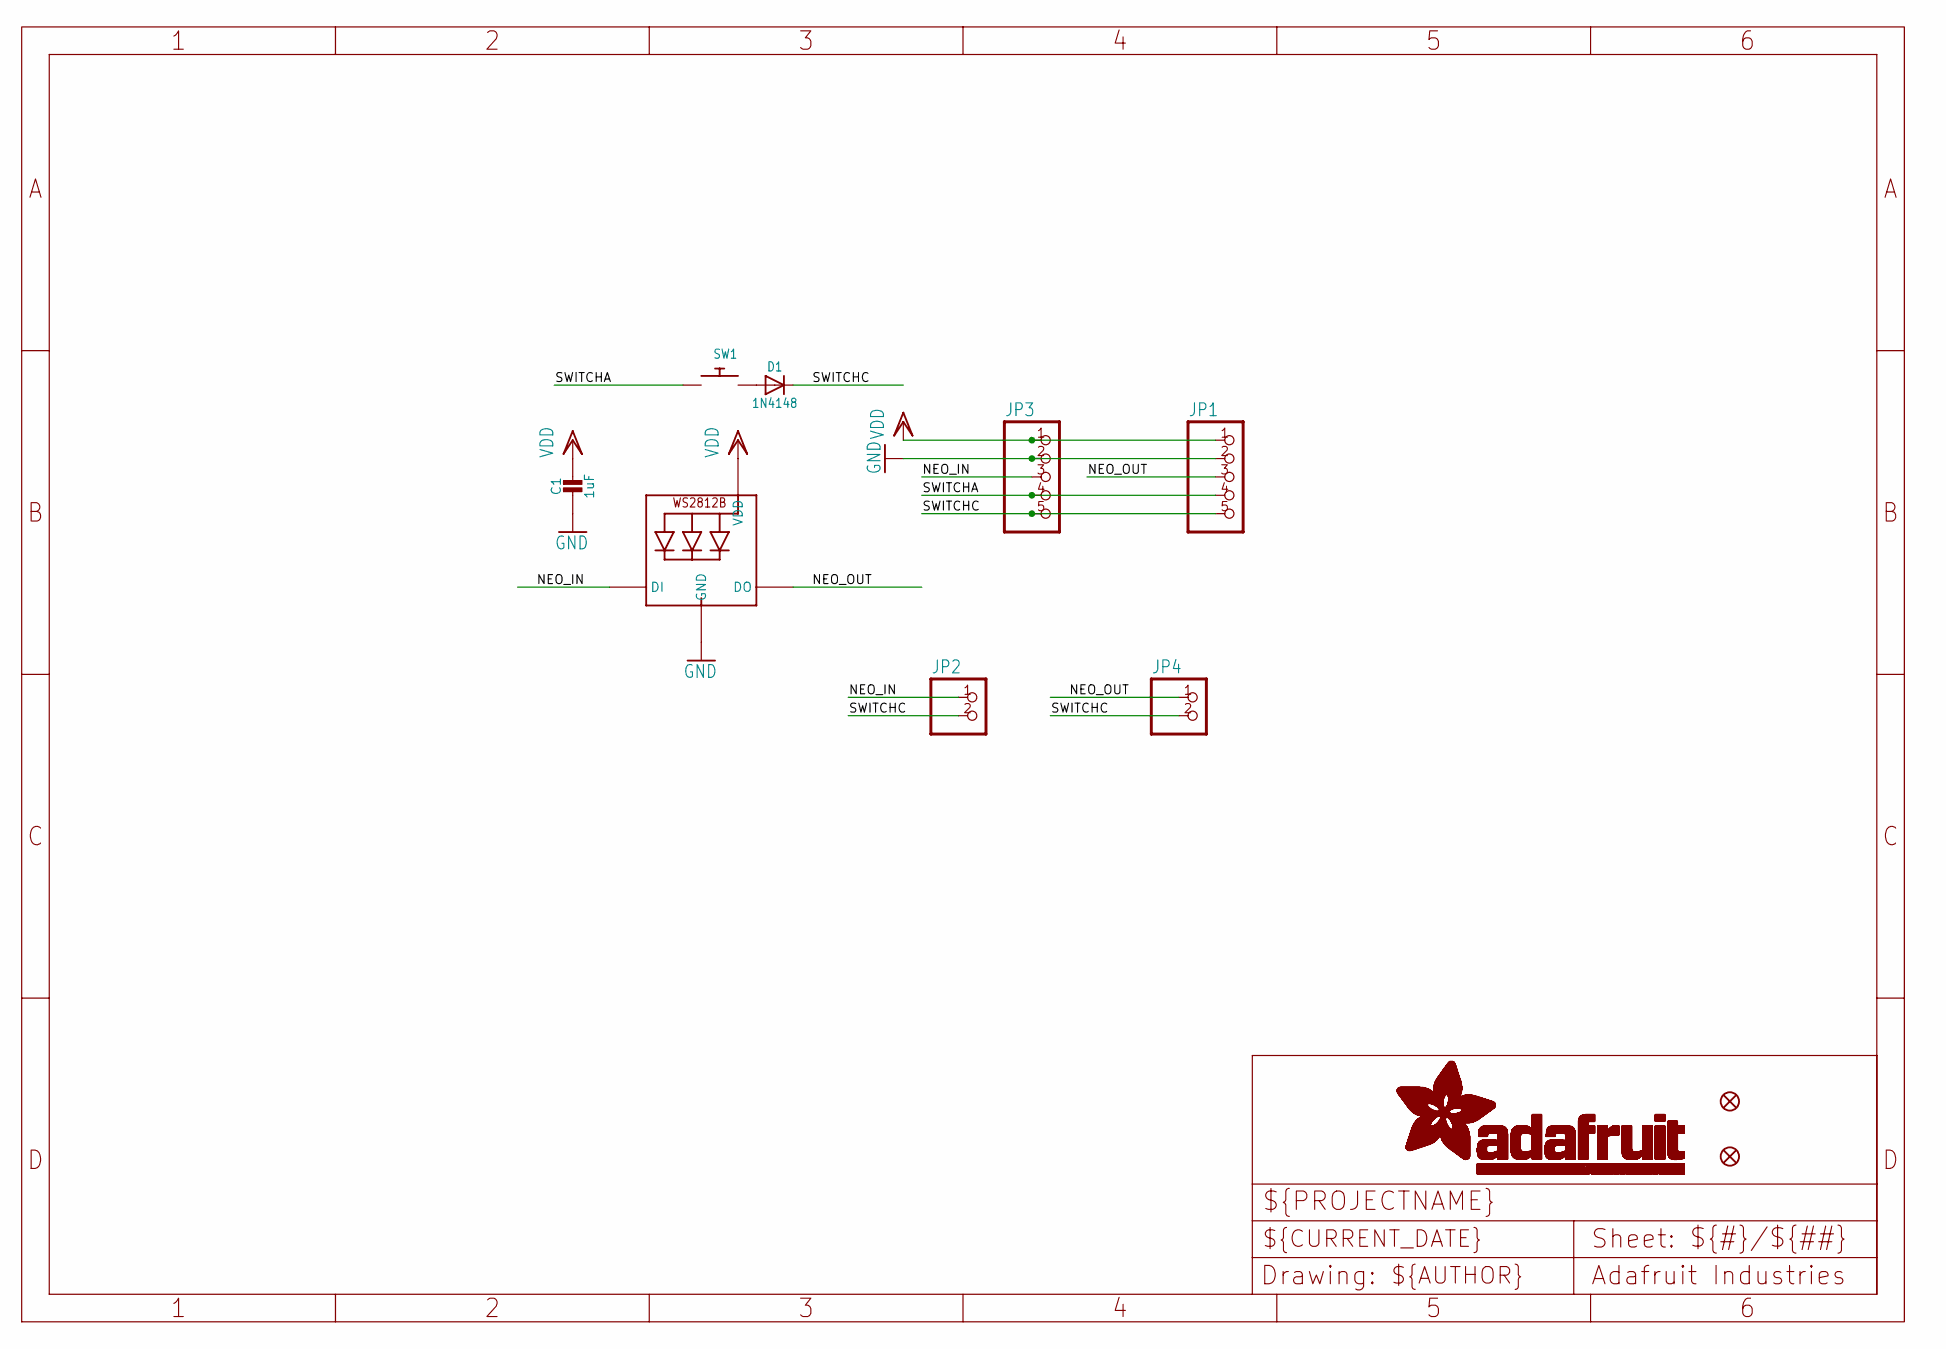
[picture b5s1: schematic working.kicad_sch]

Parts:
C1: 1uF; 0603-NO
D1: 1N4148; SOD-323
FID3, FID4: FIDUCIAL_1MM
JP1, JP3: HEADER-1X570MIL; 1X05_ROUND_70
JP2, JP4: HEADER-1X2ROUND; 1X02_ROUND
LED1: WS2812B_SK6812E; NEO3535_REVERSE
SW1: SWITCH_PUSHBUTTON_KAILH_SOCKET; KAILH_SOCKET

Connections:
GND: C1.2, JP1.2, JP3.2, LED1.3-GND (GND)
unnamed: D1.A, SW1.1
NEO_IN: JP2.1, JP3.3, LED1.4-DIN (DI)
NEO_OUT: JP1.3, JP4.1, LED1.2-DOUT (DO)
SWITCHA: JP1.4, JP3.4, SW1.2
SWITCHC: D1.C, JP1.5, JP2.2, JP3.5, JP4.2
VDD: C1.1, JP1.1, JP3.1, LED1.1-VDD (VDD)
